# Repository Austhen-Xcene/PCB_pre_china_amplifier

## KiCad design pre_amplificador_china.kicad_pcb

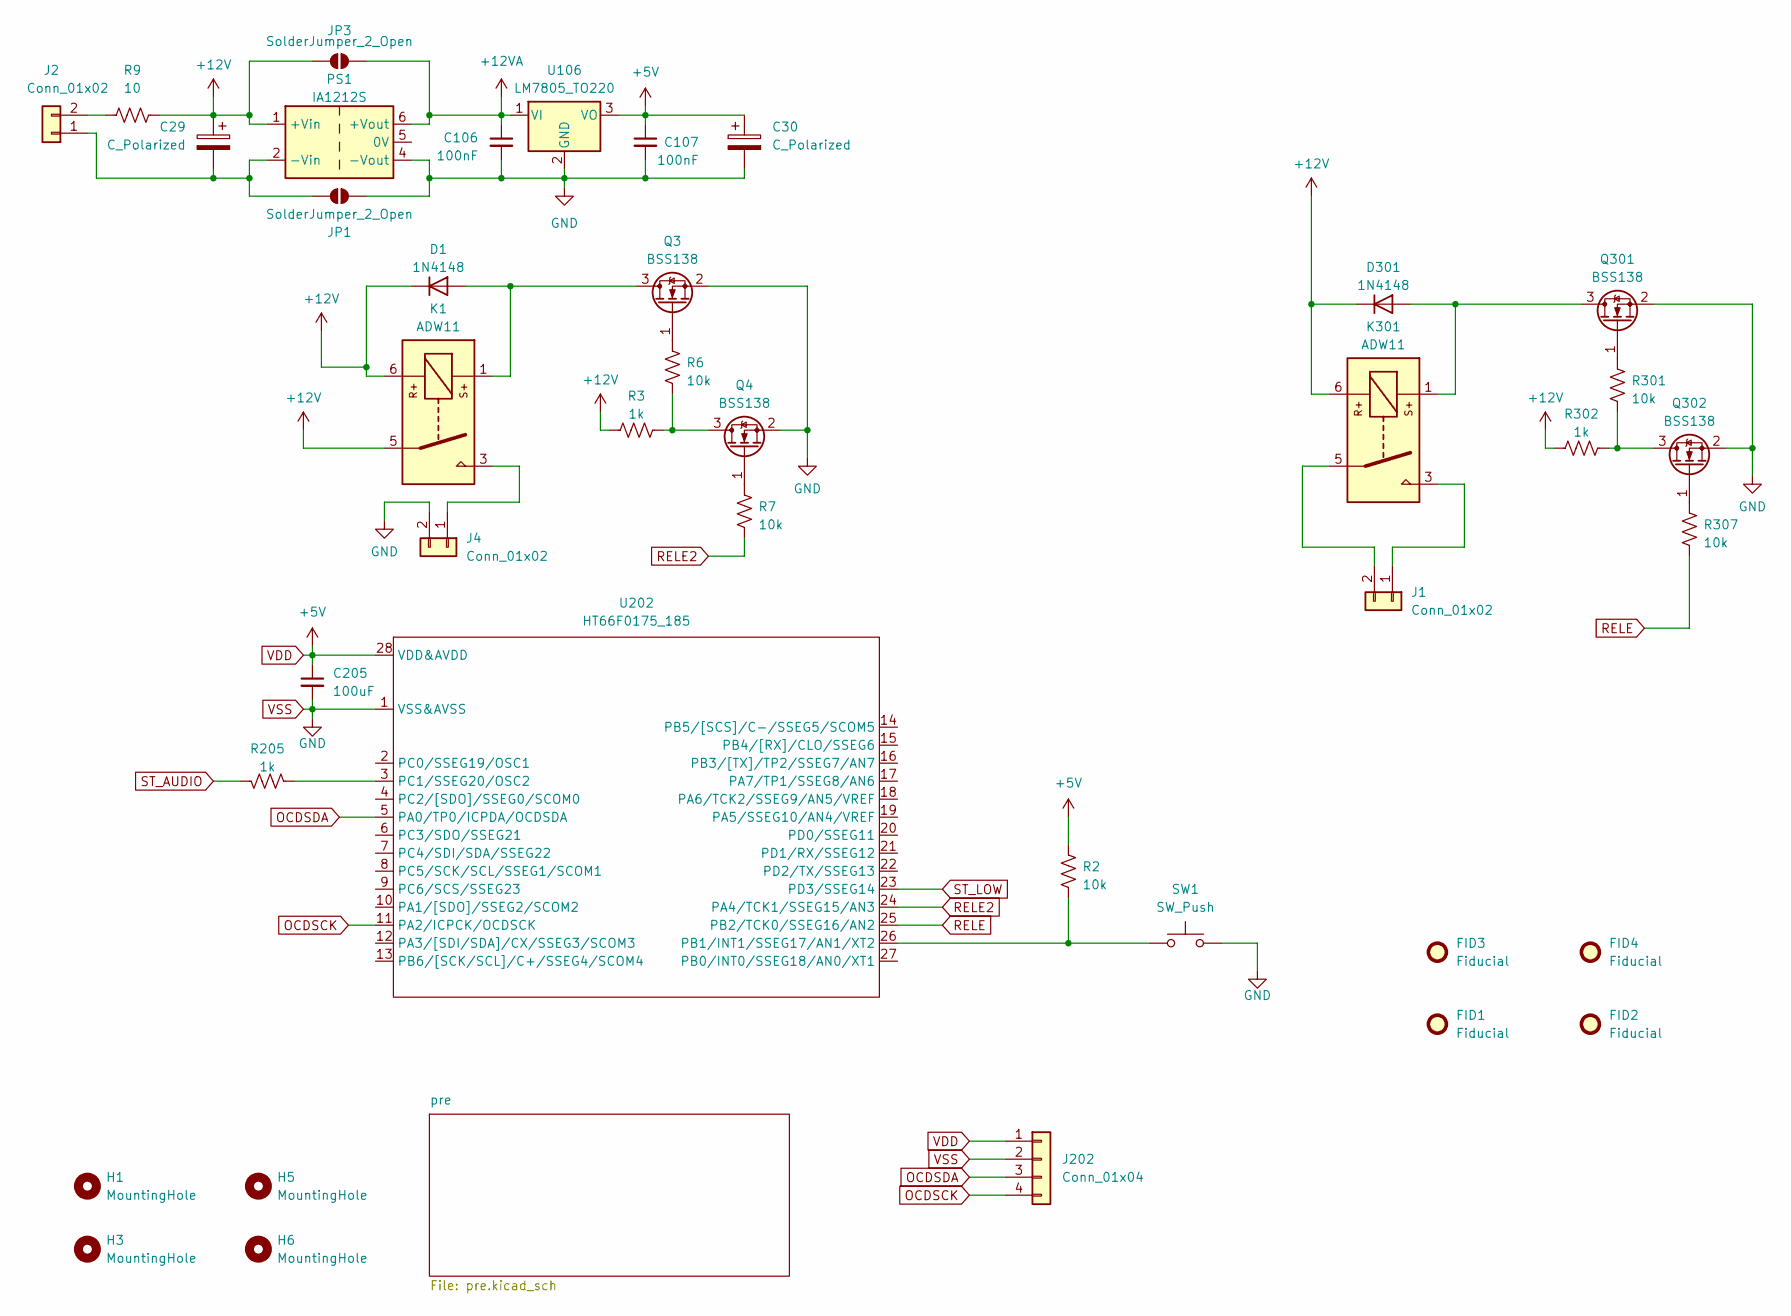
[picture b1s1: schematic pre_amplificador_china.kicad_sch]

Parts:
C29, C30: C_Polarized; CP_Radial_D10.0mm_P2.50mm_P5.00mm
C106, C107: 100nF; C_0805_2012Metric
C205: 100uF; C_0805_2012Metric
D1, D301: 1N4148; D_MiniMELF
FID1, FID2, FID3, FID4: Fiducial; Fiducial_1.5mm_Mask3mm
H1, H3, H5, H6: MountingHole; MountingHole_3.5mm
J1, J2, J4: Conn_01x02; PhoenixContact_MCV_1,5_2-G-5.08_1x02_P5.08mm_Vertical
J202: Conn_01x04; PinSocket_1x04_P2.54mm_Vertical
JP1, JP3: SolderJumper_2_Open; SolderJumper-2_P1.3mm_Open_RoundedPad1.0x1.5mm
K1, K301: ADW11; TRA2F
PS1: IA1212S; Converter_DCDC_XP_POWER-IAxxxxS_THT
Q3, Q4, Q301, Q302: BSS138; SOT-23
R2, R6, R7, R301, R307: 10k; R_0805_2012Metric
R3, R205, R302: 1k; R_0805_2012Metric
R9: 10; R_Axial_DIN0414_L11.9mm_D4.5mm_P5.08mm_Vertical
SW1: SW_Push; Button
U106: LM7805_TO220; TO-220-3_Vertical
U202: HT66F0175_185; SSOP-28_3.9x9.9mm_P0.635mm

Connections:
+12V: C29.1, D1.1 (K), D301.1 (K), JP3.2 (B), K1.5, K1.6, K301.6, PS1.1 (+Vin), R3.2, R9.1, R302.2
+12VA: C106.1, JP3.1 (A), PS1.6 (+Vout), U106.1 (VI); also elsewhere on the board
unnamed: D1.2 (A), K1.1, Q3.3 (D)
unnamed: D301.2 (A), K301.1, Q301.3 (D)
unnamed: J1.1, K301.3
unnamed: J1.2, K301.5
unnamed: C29.2, J2.1, JP1.2 (B), PS1.2 (-Vin)
unnamed: J2.2, R9.2
unnamed: J4.1, K1.3
unnamed: Q3.1 (G), R6.2
unnamed: Q4.3 (D), R3.1, R6.1
unnamed: Q4.1 (G), R7.2
unnamed: Q301.1 (G), R301.2
unnamed: Q302.3 (D), R301.1, R302.1
unnamed: Q302.1 (G), R307.2
unnamed: R2.1, SW1.1, U202.26 (PB1/INT1/SSEG17/AN1/XT2)
unnamed: R205.1, U202.3 (PC1/SSEG20/OSC2)
OCDSCK: J202.4, U202.11 (PA2/ICPCK/OCDSCK)
OCDSDA: J202.3, U202.5 (PA0/TP0/ICPDA/OCDSDA)
RELE: R307.1, U202.25 (PB2/TCK0/SSEG16/AN2)
RELE2: R7.1, U202.24 (PA4/TCK1/SSEG15/AN3)
ST_AUDIO: R205.2; also elsewhere on the board
ST_LOW: U202.23 (PD3/SSEG14); also elsewhere on the board
VDD: C30.1, C107.1, C205.1, J202.1, R2.2, U106.3 (VO), U202.28 (VDD&AVDD); also elsewhere on the board
VSS: C30.2, C106.2, C107.2, C205.2, J4.2, J202.2, JP1.1 (A), PS1.4 (-Vout), Q3.2 (S), Q4.2 (S), Q301.2 (S), Q302.2 (S), SW1.2, U106.2 (GND), U202.1 (VSS&AVSS); also elsewhere on the board

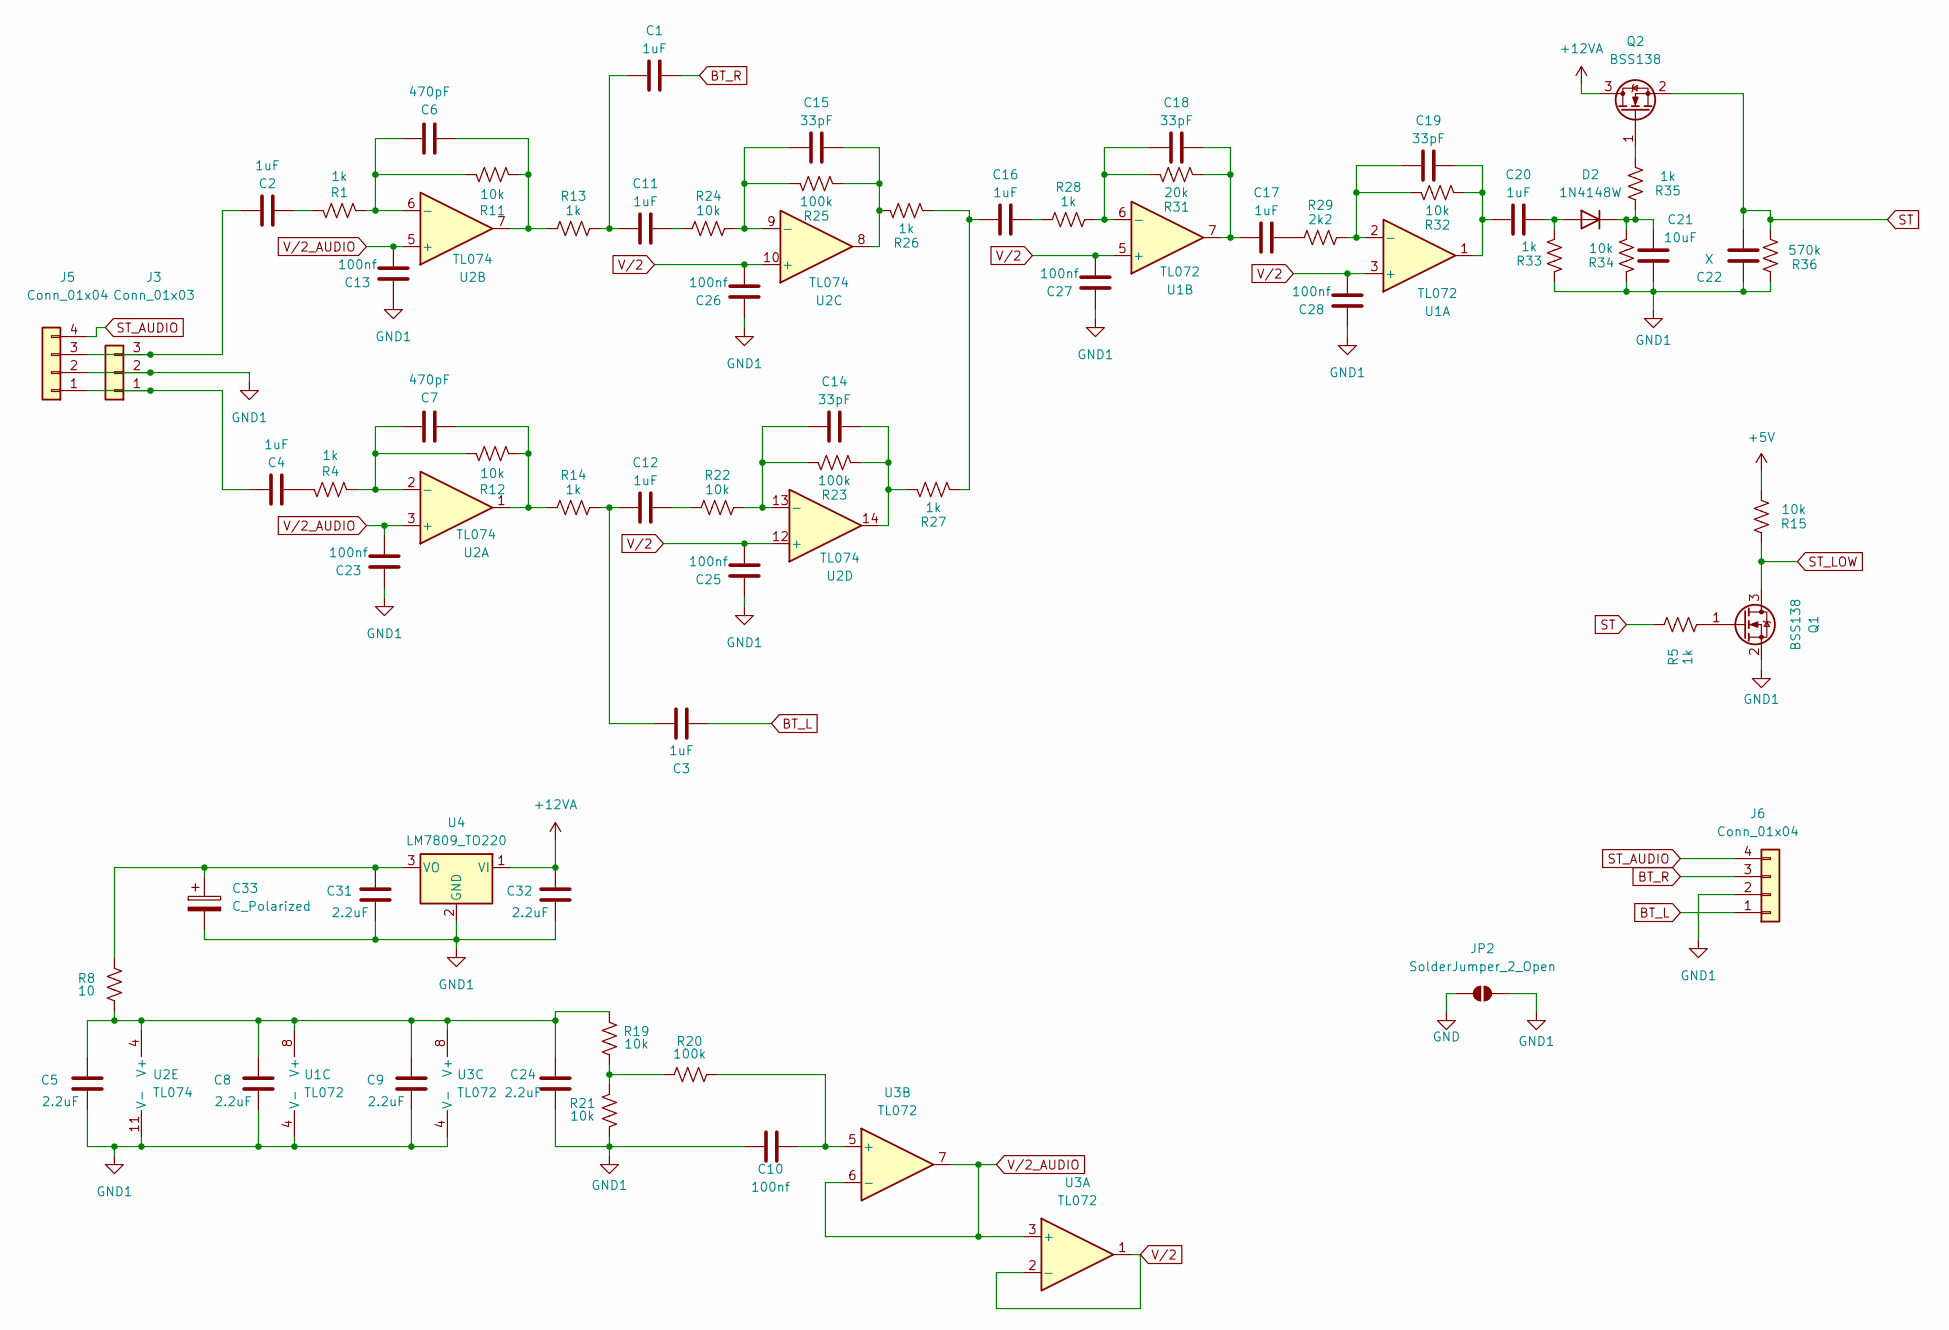
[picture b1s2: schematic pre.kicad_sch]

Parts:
C1, C2, C3, C4, C11, C12, C16, C17, C20: 1uF; C_0805_2012Metric
C5, C8, C9, C24, C31, C32: 2.2uF; C_0805_2012Metric
C6, C7: 470pF; C_0805_2012Metric
C10, C13, C23, C25, C26, C27, C28: 100nf; C_0805_2012Metric
C14, C15, C18, C19: 33pF; C_0805_2012Metric
C21: 10uF; C_0805_2012Metric
C22: X; C_0805_2012Metric
C33: C_Polarized; CP_Radial_D10.0mm_P2.50mm_P5.00mm
D2: 1N4148W; D_SOD-123
J3: Conn_01x03; JST_XH_B3B-XH-A_1x03_P2.50mm_Vertical
J5, J6: Conn_01x04; JST_XA_B04B-XASK-1-A_1x04_P2.50mm_Vertical
JP2: SolderJumper_2_Open; SolderJumper-2_P1.3mm_Open_RoundedPad1.0x1.5mm
Q1, Q2: BSS138; SOT-23
R1, R4, R5, R13, R14, R26, R27, R28, R33, R35: 1k; R_0805_2012Metric
R8: 10; R_0805_2012Metric
R11, R12, R15, R19, R21, R22, R24, R32, R34: 10k; R_0805_2012Metric
R20, R23, R25: 100k; R_0805_2012Metric
R29: 2k2; R_0805_2012Metric
R31: 20k; R_0805_2012Metric
R36: 570k; R_0805_2012Metric
U1, U3: TL072; SOIC-8_3.9x4.9mm_P1.27mm
U2: TL074; SOIC-14_3.9x8.7mm_P1.27mm
U4: LM7809_TO220; TO-220-3_Vertical

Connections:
+12VA: C32.1, Q2.3 (D), U4.1 (VI); also elsewhere on the board
BT_L: C3.2, J6.1
BT_R: C1.1, J6.3
GND1: C5.2, C8.2, C9.2, C10.1, C13.2, C21.1, C22.1, C23.2, C24.2, C25.2, C26.2, C27.2, C28.2, C31.2, C32.2, C33.2, J3.2, J5.2, J6.2, JP2.2 (B), Q1.2 (S), R21.2, R33.2, R34.2, R36.2, U1.4 (V-), U2.11 (V-), U3.4 (V-), U4.2 (GND)
unnamed: C1.2, C11.1, R13.1
unnamed: C2.1, R1.2
unnamed: C4.1, R4.2
unnamed: C6.1, R11.1, R13.2, U2.7
unnamed: C7.1, R12.1, R14.2, U2.1
unnamed: C11.2, R24.2
unnamed: C3.1, C12.1, R14.1
unnamed: C12.2, R22.2
unnamed: C14.2, R23.1, R27.2, U2.14
unnamed: C15.2, R25.1, R26.2, U2.8
unnamed: C16.1, R26.1, R27.1
unnamed: C16.2, R28.2
unnamed: C17.1, C18.2, R31.1, U1.7
unnamed: C17.2, R29.2
unnamed: C19.2, C20.1, R32.1, U1.1
unnamed: C20.2, D2.2 (A), R33.1
unnamed: C21.2, D2.1 (K), R34.1, R35.2
unnamed: C4.2, J3.1, J5.1
unnamed: C2.2, J3.3, J5.3
unnamed: Q1.1 (G), R5.1
unnamed: Q2.1 (G), R35.1
unnamed: R19.2, R20.1, R21.1
unnamed: C19.1, R29.1, R32.2, U1.2 (-)
unnamed: C18.1, R28.1, R31.2, U1.6 (-)
unnamed: C5.1, C8.1, C9.1, C24.1, R8.1, R19.1, U1.8 (V+), U2.4 (V+), U3.8 (V+)
unnamed: C7.2, R4.1, R12.2, U2.2 (-)
unnamed: C6.2, R1.1, R11.2, U2.6 (-)
unnamed: C15.1, R24.1, R25.2, U2.9 (-)
unnamed: C14.1, R22.1, R23.2, U2.13 (-)
unnamed: C10.2, R20.2, U3.5 (+)
unnamed: C31.1, C33.1, R8.2, U4.3 (VO)
ST: C22.2, Q2.2 (S), R5.2, R36.1
ST_AUDIO: J5.4, J6.4; also elsewhere on the board
ST_LOW: Q1.3 (D), R15.2; also elsewhere on the board
VDD: R15.1; also elsewhere on the board
VSS: JP2.1 (A); also elsewhere on the board
V/2: C25.1, C26.1, C27.1, C28.1, U1.3 (+), U1.5 (+), U2.10 (+), U2.12 (+), U3.1, U3.2 (-)
V/2_AUDIO: C13.1, C23.1, U2.3 (+), U2.5 (+), U3.3 (+), U3.6 (-), U3.7

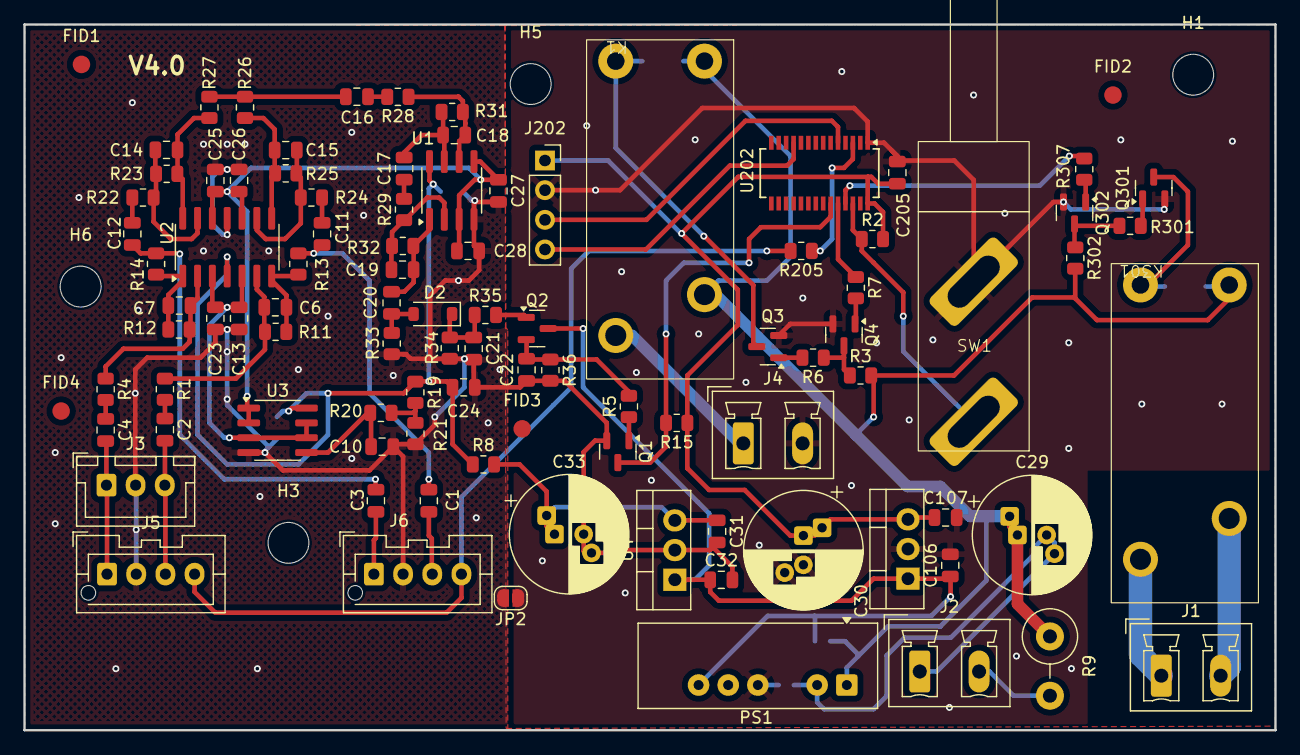
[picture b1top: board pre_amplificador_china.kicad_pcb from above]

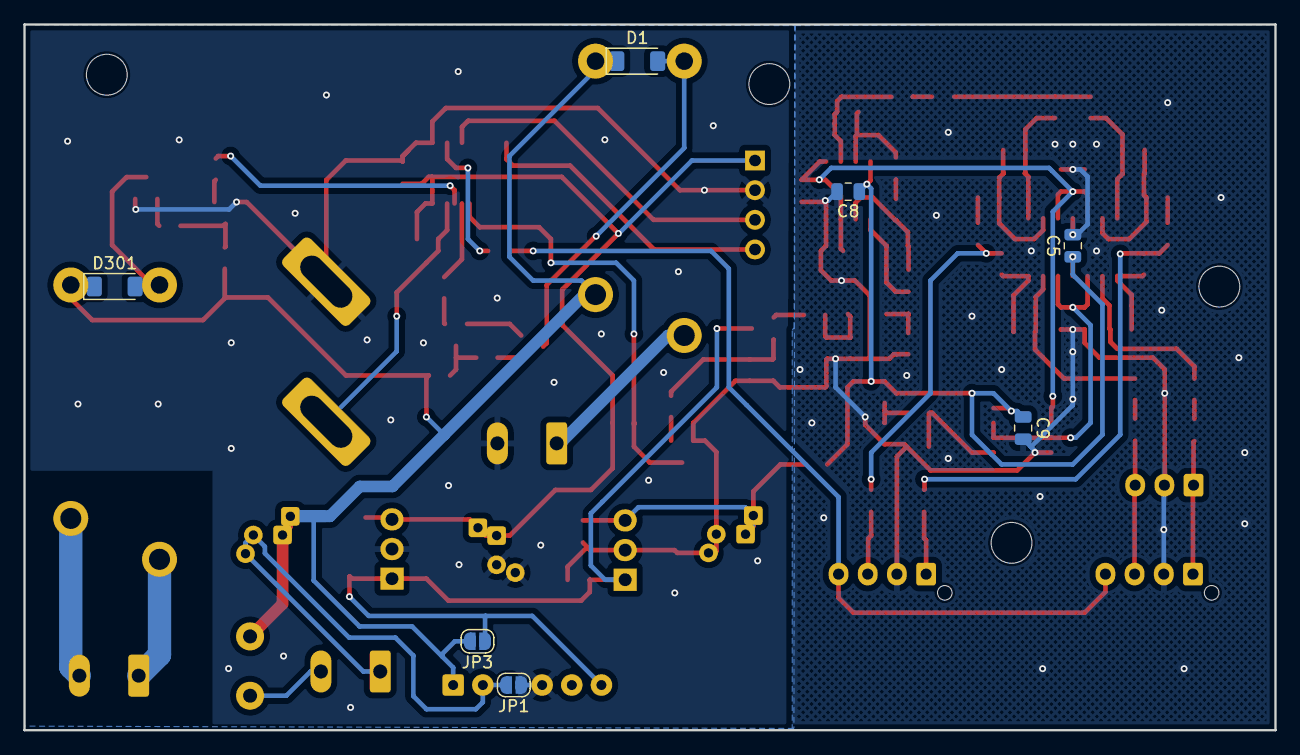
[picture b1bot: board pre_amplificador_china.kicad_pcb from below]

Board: 2 copper layers, 107.2 x 60.5 mm, 108 parts (7 on the bottom side), 62 nets.

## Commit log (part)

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2026-01-22 first comit
2026-01-22 arquivos de fabricacao
2026-01-23 correcao de standby no IC
2026-02-12 gnerate bom list
2026-06-17 v2.0 pre APL_STA2150
